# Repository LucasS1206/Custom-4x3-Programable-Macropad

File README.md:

# Custom 4x3 Macropad (with Rotary Encoder & OLED)
A custom 4x3 mechanical macropad I designed and built from scratch. This was designed for the intention of a dedicated keypad for a daily computer setup. I used this project as an opportunity to walk through the entire hardware development process from designing the circuit board in KiCad to writing the embedded C firmware in QMK.

## System Features
Layout: A 4x3 grid (12 keys) for custom shortcuts and macros.

Rotary Encoder: An EC11 clickable dial for master volume and media control.

Display: A 1.3" SH1106 OLED screen for real-time visual feedback.

Microcontroller: Pro Micro RP2040.

Firmware: Custom QMK integration, giving me complete control over every key switch, screen display, and dial action.

## Hardware Design (KiCad)
The hardware architecture and PCB were developed using KiCad 10.0:

Schematics: Built a 4x3 switch matrix with diodes to prevent key ghosting, alongside the specific pin routing for the encoder and microcontroller.

PCB Layout: Routed a compact, custom circuit board.

Iterative Design: During the layout phase, I caught and fixed an orientation error with the microcontroller footprint and adjusted the top-layer copper pour clearances to make sure the board would manufacture correctly without short-circuiting.

## QMK Firmware
The /firmware directory contains the configuration files (keymap.c, keyboard.json, config.h, and rules.mk) required to run the system.

## Repository Structure
/Hardware: The primary KiCad 10.0 design files (.kicad_pro, .kicad_sch, .kicad_pcb).

/firmware/testpad: The custom QMK configuration source files.

/Images: System documentation through images of all parts of the design proccess.

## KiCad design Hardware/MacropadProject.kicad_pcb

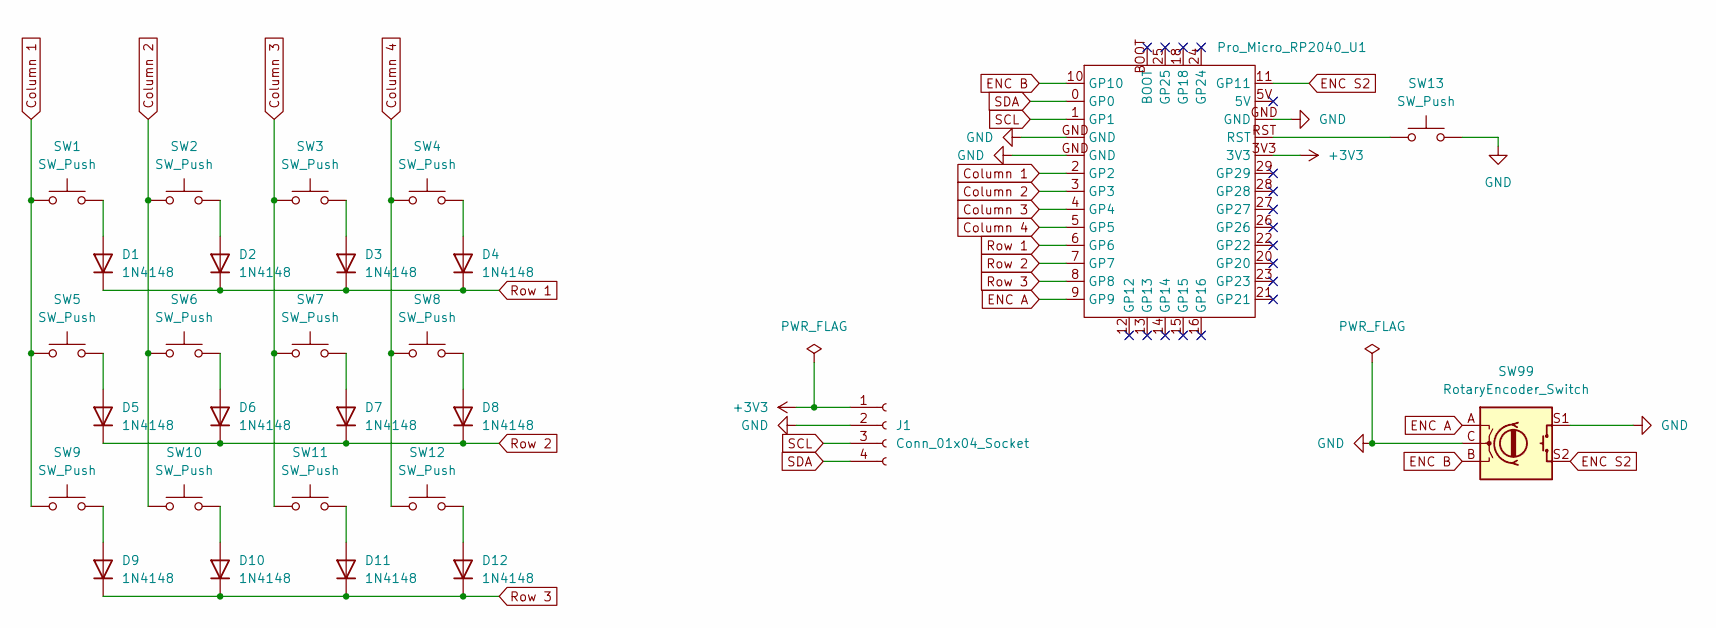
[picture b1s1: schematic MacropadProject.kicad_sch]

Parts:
D1, D2, D3, D4, D5, D6, D7, D8, D9, D10, D11, D12: 1N4148; D_DO-35_SOD27_P7.62mm_Horizontal
J1: Conn_01x04_Socket; PinSocket_1x04_P2.54mm_Vertical
Pro_Micro_RP2040_U1: pro_micro_rp2040
SW1, SW2, SW3, SW4, SW5, SW6, SW7, SW8, SW9, SW10, SW11, SW12, SW13: SW_Push; MX-Solderable-1U
SW99: RotaryEncoder_Switch; RotaryEncoder_Alps_EC11E-Switch_Vertical_H20mm

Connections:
+3V3: J1.1, Pro_Micro_RP2040_U1.3V3
Column 1: Pro_Micro_RP2040_U1.2 (GP2), SW1.1, SW5.1, SW9.1
Column 2: Pro_Micro_RP2040_U1.3 (GP3), SW2.1, SW6.1, SW10.1
Column 3: Pro_Micro_RP2040_U1.4 (GP4), SW3.1, SW7.1, SW11.1
Column 4: Pro_Micro_RP2040_U1.5 (GP5), SW4.1, SW8.1, SW12.1
ENC A: Pro_Micro_RP2040_U1.9 (GP9), SW99.A
ENC B: Pro_Micro_RP2040_U1.10 (GP10), SW99.B
ENC S2: Pro_Micro_RP2040_U1.11 (GP11), SW99.S2
GND: J1.2, Pro_Micro_RP2040_U1.GND, SW13.2, SW99.C, SW99.S1
unnamed: D1.2 (A), SW1.2
unnamed: D2.2 (A), SW2.2
unnamed: D3.2 (A), SW3.2
unnamed: D4.2 (A), SW4.2
unnamed: D5.2 (A), SW5.2
unnamed: D6.2 (A), SW6.2
unnamed: D7.2 (A), SW7.2
unnamed: D8.2 (A), SW8.2
unnamed: D9.2 (A), SW9.2
unnamed: D10.2 (A), SW10.2
unnamed: D11.2 (A), SW11.2
unnamed: D12.2 (A), SW12.2
unnamed: Pro_Micro_RP2040_U1.RST, SW13.1
Row 1: D1.1 (K), D2.1 (K), D3.1 (K), D4.1 (K), Pro_Micro_RP2040_U1.6 (GP6)
Row 2: D5.1 (K), D6.1 (K), D7.1 (K), D8.1 (K), Pro_Micro_RP2040_U1.7 (GP7)
Row 3: D9.1 (K), D10.1 (K), D11.1 (K), D12.1 (K), Pro_Micro_RP2040_U1.8 (GP8)
SCL: J1.3, Pro_Micro_RP2040_U1.1 (GP1)
SDA: J1.4, Pro_Micro_RP2040_U1.0 (GP0)

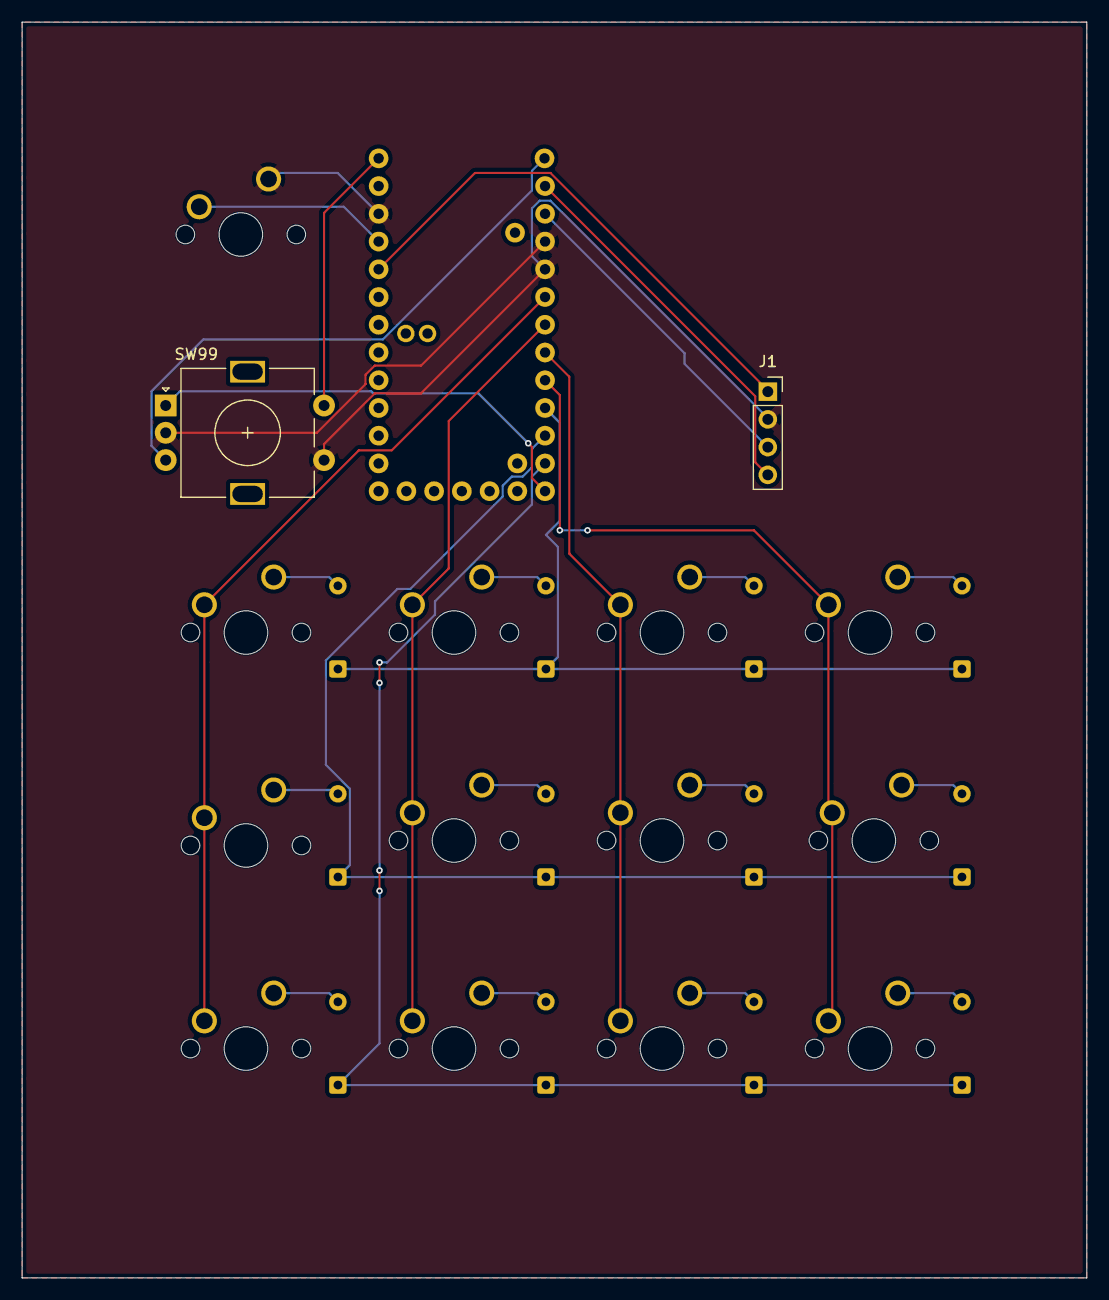
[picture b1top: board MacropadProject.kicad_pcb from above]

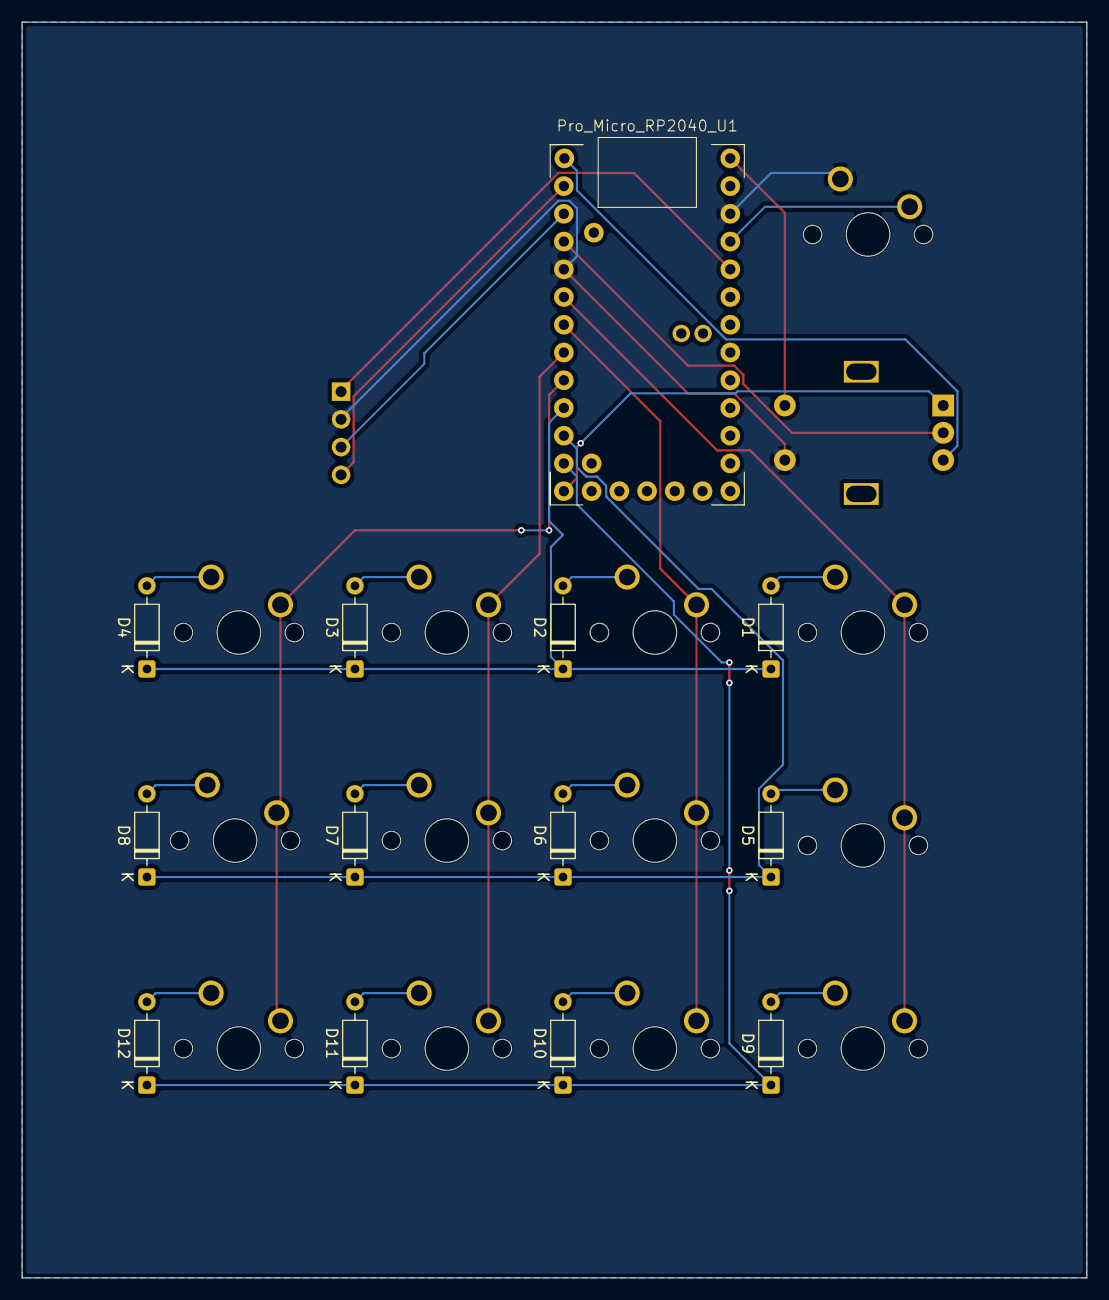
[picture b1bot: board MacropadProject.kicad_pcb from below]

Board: 2 copper layers, 97.5 x 115.0 mm, 28 parts (13 on the bottom side), 27 nets.
